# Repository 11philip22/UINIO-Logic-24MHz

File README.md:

# UINIO-Logic-24MHz Logic Analyzer

[**UINIO-Logic-24MHz**](https://gitee.com/uinika/UINIO-Logic-24MHz) is a logic analyzer circuit design based on Infineon's (formerly Cypress) [**CY7C68013A**](https://www.infineon.com/cms/en/product/universal-serial-bus-usb-power-delivery-controller/peripheral-controllers/ez-usb-fx2lp/cy7c68013a-56ltxit/) `USB 2.0` controller and the [**sigrok**](https://sigrok.org/) open-source firmware. It provides a `24 MHz` sampling rate and **8** input channels.

| Front | Back |
| :---: | :---: |
|  |  |

## Design Overview

1. Uses a **USB Type-C** connector and a `10-pin` shrouded header.
2. The **CY7C68013A** USB controller uses a compact `QFN-56` package.
3. The **AT24C64** EEPROM from Microchip uses a compact `TSSOP-8` package.
4. Includes an onboard `24 MHz` passive SMD crystal; all SMD resistors and capacitors use the compact `0402` package.
5. Adds a **74HC245** eight-channel bus transceiver with **tri-state outputs** for more reliable signal acquisition.
6. The low-dropout regulator can use an **LDO** such as the `ME6211C33M5G` or `A6303AE5R-33A` in an `SOT-23-5` package.
7. Adds a set of TVS diodes for transient-voltage protection at the **USB Type-C** connector.

## Notes

- LED `D2` is connected to the **CY7C68013A** `PA0` pin, while `D3` is connected to `PA1`.
- Use the [sigrok-firmware-fx2lafw](https://github.com/wuxx/sigrok-firmware-fx2lafw) open-source firmware with the [PulseView](https://sigrok.org/wiki/Downloads) desktop application.

## Technical Documentation

[UinIO.com Electronics Technology Lab](http://uinio.com/) provides the following technical resources for the open-source **UINIO-Logic-24MHz** project:

- [UINIO-Logic-24MHz Core Board Schematic](http://uinio.com/my/works/UINIO-Logic-24MHz/UINIO-Logic-24MHz-Schematic.pdf)
- [Interactive BOM and PCB Layout Preview](http://uinio.com/archives/BOM/UINIO-Logic-24MHz.html)
- [UINIO-Logic-24MHz Logic Analyzer Quick Start Guide](http://uinio.com/Project/UINIO-Logic-24MHz/)

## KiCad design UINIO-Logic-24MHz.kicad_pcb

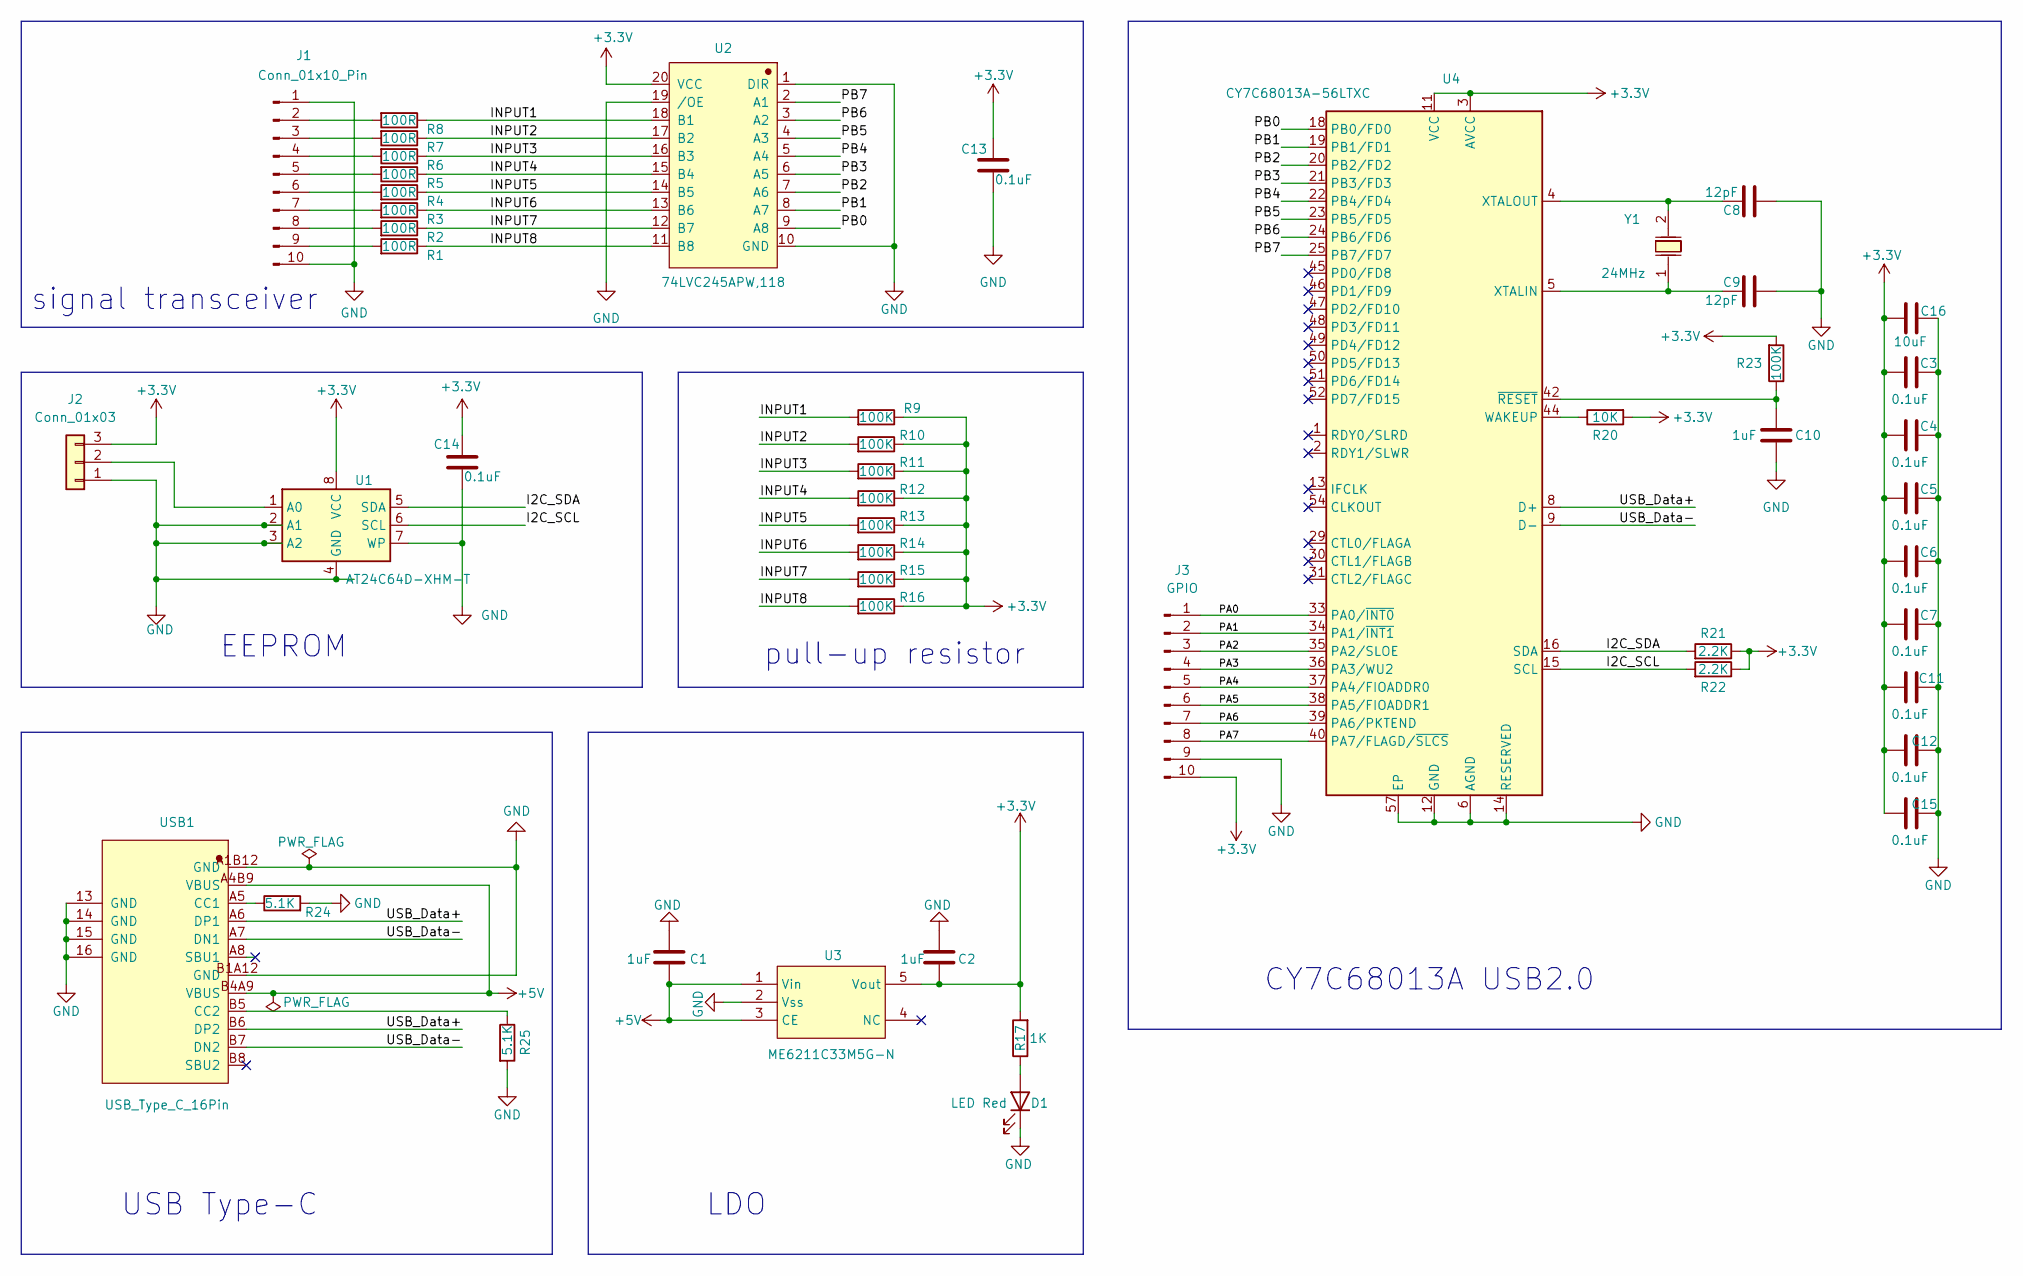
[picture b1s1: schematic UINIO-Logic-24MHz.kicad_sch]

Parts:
C1, C2: 1uF; C_0603_1608Metric; LCSC Part # C15849
C3, C4, C5, C6, C7, C11, C12, C13, C14, C15: 0.1uF; C_0402_1005Metric; LCSC Part # C1525
C8, C9: 12pF; C_0402_1005Metric; LCSC Part # C1547
C10: 1uF; C_0402_1005Metric; LCSC Part # C52923
C16: 10uF; C_0805_2012Metric; LCSC Part # C15850
D1: LED Red; LED_0603_1608Metric; LCSC Part # C2286
J1: Conn_01x10_Pin; PinHeader_1x10_P2.54mm_Vertical
J2: Conn_01x03; PinHeader_1x03_P2.54mm_Vertical
J3: GPIO; PinHeader_1x10_P2.54mm_Vertical
R1, R2, R3, R4, R5, R6, R7, R8: 100R; R_0402_1005Metric; LCSC Part # C25076
R9, R10, R11, R12, R13, R14, R15, R16, R23: 100K; R_0402_1005Metric; LCSC Part # C25741
R17: 1K; R_0402_1005Metric; LCSC Part # C11702
R20: 10K; R_0402_1005Metric; LCSC Part # C25744
R21, R22: 2.2K; R_0402_1005Metric; LCSC Part # C25879
R24, R25: 5.1K; R_0603_1608Metric; LCSC Part # C23186
U1: AT24C64D-XHM-T; TSSOP-8_4.4x3mm_P0.65mm; LCSC Part # C111440
U2: 74LVC245APW,118; TSSOP-20_L6.5-W4.4-P0.65-LS6.4-BL; LCSC Part # C6082
U3: ME6211C33M5G-N; SOT-23-5_L3.0-W1.7-P0.95-LS2.8-BR; LCSC Part # C82942
U4: CY7C68013A-56LTXC; QFN-56-1EP_8x8mm_P0.5mm_EP4.5x5.2mm_ThermalVias_TopTented; LCSC Part # C14912
USB1: USB_Type_C_16Pin; USB-C-SMD_TYPEC-304J-BCP16; LCSC Part # C2835315
Y1: 24MHz; HC-49-SMD_L7.0-W3.0; MPN X49XM24MOB2SC; LCSC Part # C412889

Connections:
+3.3V: C2.2, C3.1, C4.1, C5.1, C6.1, C7.1, C11.1, C12.1, C13.2, C14.2, C15.1, C16.1, J2.3, J3.10, R9.1, R10.1, R11.1, R12.1, R13.1, R14.1, R15.1, R16.1, R17.2, R20.2, R21.1, R22.1, R23.2, U1.8 (VCC), U2.20 (VCC), U3.5 (Vout), U4.3 (AVCC), U4.7 (AVCC), U4.11 (VCC), U4.17 (VCC), U4.27 (VCC), U4.32 (VCC), U4.43 (VCC), U4.55 (VCC)
+5V: C1.2, U3.1 (Vin), U3.3 (CE), USB1.A4B9 (VBUS), USB1.B4A9 (VBUS)
/I2C_SCL: R22.2, U1.6 (SCL), U4.15 (SCL)
/I2C_SDA: R21.2, U1.5 (SDA), U4.16 (SDA)
/INPUT1: R8.1, R9.2, U2.18 (B1)
/INPUT2: R7.1, R10.2, U2.17 (B2)
/INPUT3: R6.1, R11.2, U2.16 (B3)
/INPUT4: R5.1, R12.2, U2.15 (B4)
/INPUT5: R4.1, R13.2, U2.14 (B5)
/INPUT6: R3.1, R14.2, U2.13 (B6)
/INPUT7: R2.1, R15.2, U2.12 (B7)
/INPUT8: R1.1, R16.2, U2.11 (B8)
/PA0: J3.1, U4.33 (PA0/~INT0)
/PA1: J3.2, U4.34 (PA1/~INT1)
/PA2: J3.3, U4.35 (PA2/SLOE)
/PA3: J3.4, U4.36 (PA3/WU2)
/PA4: J3.5, U4.37 (PA4/FIOADDR0)
/PA5: J3.6, U4.38 (PA5/FIOADDR1)
/PA6: J3.7, U4.39 (PA6/PKTEND)
/PA7: J3.8, U4.40 (PA7/FLAGD/~SLCS)
/PB0: U2.9 (A8), U4.18 (PB0/FD0)
/PB1: U2.8 (A7), U4.19 (PB1/FD1)
/PB2: U2.7 (A6), U4.20 (PB2/FD2)
/PB3: U2.6 (A5), U4.21 (PB3/FD3)
/PB4: U2.5 (A4), U4.22 (PB4/FD4)
/PB5: U2.4 (A3), U4.23 (PB5/FD5)
/PB6: U2.3 (A2), U4.24 (PB6/FD6)
/PB7: U2.2 (A1), U4.25 (PB7/FD7)
/USB_Data+: U4.8 (D+), USB1.A6 (DP1), USB1.B6 (DP2)
/USB_Data-: U4.9 (D-), USB1.A7 (DN1), USB1.B7 (DN2)
GND: C1.1, C2.1, C3.2, C4.2, C5.2, C6.2, C7.2, C8.1, C9.1, C10.1, C11.2, C12.2, C13.1, C14.1, C15.2, C16.2, D1.1 (K), J1.1, J1.10, J2.1, J3.9, R24.2, R25.2, U1.2 (A1), U1.3 (A2), U1.4 (GND), U1.7 (WP), U2.1 (DIR), U2.10 (GND), U2.19 (/OE), U3.2 (Vss), U4.6 (AGND), U4.10 (AGND), U4.12 (GND), U4.14 (RESERVED), U4.26 (GND), U4.28 (GND), U4.41 (GND), U4.53 (GND), U4.56 (GND), U4.57 (EP), USB1.13 (GND), USB1.14 (GND), USB1.15 (GND), USB1.16 (GND), USB1.A1B12 (GND), USB1.B1A12 (GND)
unnamed: D1.2 (A), R17.1
unnamed: J1.2, R8.2
unnamed: J1.3, R7.2
unnamed: J1.4, R6.2
unnamed: J1.5, R5.2
unnamed: J1.6, R4.2
unnamed: J1.7, R3.2
unnamed: J1.8, R2.2
unnamed: J1.9, R1.2
unnamed: J2.2, U1.1 (A0)
unnamed: R20.1, U4.44 (WAKEUP)
unnamed: C9.2, U4.5 (XTALIN), Y1.1 (OSC1)
unnamed: C8.2, U4.4 (XTALOUT), Y1.2 (OSC2)
unnamed: C10.2, R23.1, U4.42 (~RESET)
unnamed: R24.1, USB1.A5 (CC1)
unnamed: R25.1, USB1.B5 (CC2)

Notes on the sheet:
CY7C68013A USB2.0
LDO
signal transceiver
pull-up resistor
USB Type-C
EEPROM

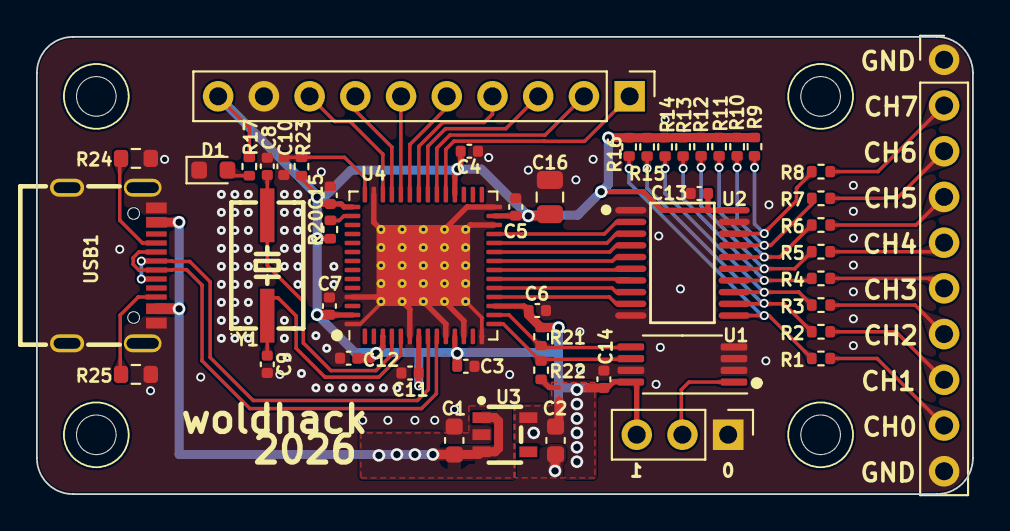
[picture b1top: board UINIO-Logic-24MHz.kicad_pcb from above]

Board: 2 copper layers, 52.0 x 25.4 mm, 53 parts (0 on the bottom side), 47 nets.

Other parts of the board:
HOLE1, HOLE2, HOLE3, HOLE4: Hole-2mm
